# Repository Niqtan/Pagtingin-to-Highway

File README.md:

# Pagtingin (Obstacle Detecting Glasses) 2.0

## Project Aims

The Pagtingin obstacle detecting glasses aims to help visually impaired people to easily detect obstacles in front of them through innovative glasses. While traditional walking sticks indeed help in detecting obstacles on the ground, they often fail to identify objects at chest or head level, such as low-hanging branches, open cabinets, or protruding signs. 

Hence, Pagtingin aims to aid this limitation and ensure a safe journey of navigation. Whether indoors or outdoors, the device will be able to identify potential hazards through a Time-of-Flight sensor and send real-time audio feedback, which helps users to be much more confident and safe in the user's day-to-day lives.

Pagtingin 2.0 uses a modular approach instead of a tightly coupled design, making the system easier to iterate on and refine over time. Some design changes and iterations also have been made.

## Zine
[Click here for beautiful zine page](PAGTINGIN_2.0.pdf)

## Prototype Concept

## PCB 

### Main Module

Image 1. Main PCB Module Front View

Image 2. Main PCB Module Backk View

### Audio Module

Image 3. Audio PCB Module Front View

Image 4. Audio PCB Module Back View

### Sensor Module

Image 5. Sensor PCB Module Front View

Image 6. Sensor PCB Module Back View

## CAD

### Glasses Frame (with new hinges)

Image 7. Glasses Frame Front View

Image 8. Glasses Side View

Image 9. Glasses Frame Back View

### Temples

Image 10. Glasses Rail Side View

Image 11. Glasses Temple Top View

### Module Pod

## 3D Printing
In terms of 3D printing, it might be better to print this in resin since the glasses frame will require precise dimensions. You may be able to print this in FDM, but it is recommended for the parameters to be as precise as possible.

## Making your own glasses!

Phase 1: Ordering the PCB 

For ordering this PCB, I would recommend using JLCPCB as the manufacturer. Use the PCBA assembly option and go through the interface!

Here are some parameters you should know:

Thickness: 0.8 mm or 1.0 mm
Surface finish: HASL (with lead) or ENIG
Copper weight 1 oz

Phase 2: 3D Printing 

Use your favorite slicer and 3D print it up! 

Material for the temples: PETG / PLA
Material for frame: Resin

Once you 3D  print it, you can start assembling it like normal glasses!

Phase 3: Firmware

Flash the firmware with the test code provided.

## BOM

### Main Module
[MainModule.csv](BOM.csv)

### Sensor Module
[SensorModule.csv](BOM3.csv)

### Audio Module
[AudioModule.csv](BOM2.csv)

## Firmware
Still in progress. You may see previous prototypes in the folder for previous version's firmware. But for the firmware, I am planning to use the ESP-IDF in programming it. I chose the ESP-IDF because it allows full control over the ESP32-PICO-D4's peripherals and such. (also because I wanna challenge myself)

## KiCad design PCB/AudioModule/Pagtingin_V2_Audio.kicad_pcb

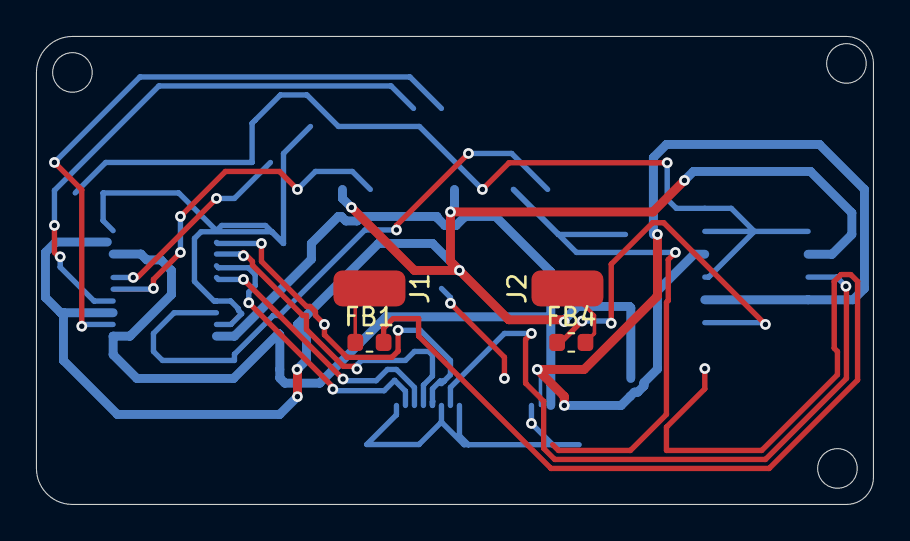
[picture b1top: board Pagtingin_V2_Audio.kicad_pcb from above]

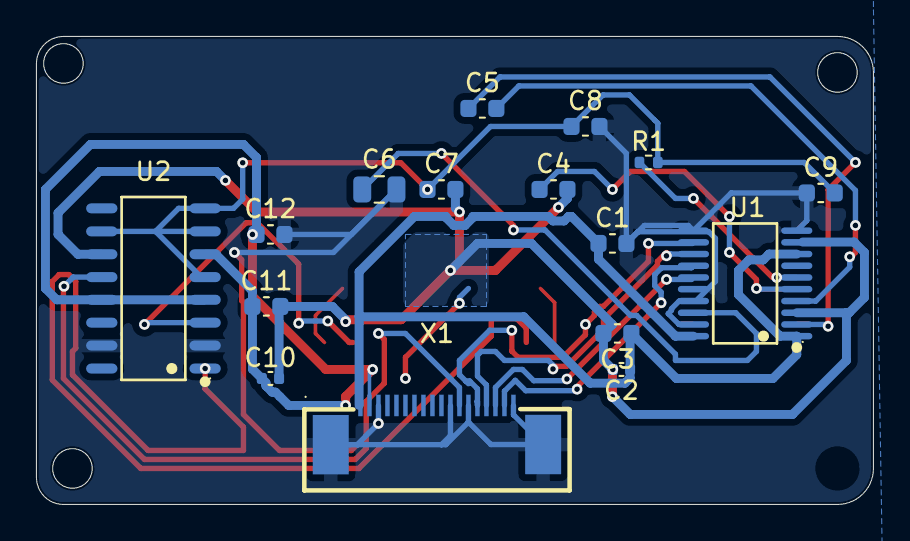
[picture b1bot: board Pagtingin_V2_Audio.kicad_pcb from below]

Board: 2 copper layers, 46.5 x 26.0 mm, 20 parts (16 on the bottom side), 19 nets.

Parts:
C1, C3, C5, C7, C8, C9, C11, C12: 1µ; C_0603_1608Metric
C2, C10: 0.1µ; C_0402_1005Metric
C4: 2.2µ; C_0603_1608Metric
C6: 10µ; C_0805_2012Metric
FB1, FB4: MAF1608FAD151CT000; L_0603_1608Metric
J1, J2: Conn_01x01_Pin; SolderWirePad_1x01_SMD_2x4mm
R1: 1k; R_0402_1005Metric
U1: PCM5102; TSSOP-20_L6.5-W4.4-P0.65-LS6.4-BL
U2: PAM8403DR; SOP-16_L10.0-W3.9-P1.27-LS6.0-BL
X1: AFC07-S18FCA-00; FPC-SMD_AFC07-S18FCA-00

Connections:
+3.3V: C1.1, C2.1, C3.1, U1.1 (CPVDD), U1.8 (AVDD), U1.20 (DVDD), X1.1
+5V: C10.1, C11.1, C12.1, U2.4 (PVDD@1), U2.6 (VDD), U2.13 (PVDD@2), X1.2
/AUDIO_OUT_L: C7.1, C8.1, C9.2, R1.2, U2.5 (MUTE), U2.7 (INL), U2.8 (VREF), U2.10 (INR)
/IO23 (MCU): U2.12 (SHND), X1.12
/IO26 (MCU): U1.12 (SCK), X1.14
/IO27 (MCU): U1.13 (BCK), X1.15
/IO32 (MCU): U1.15 (LRCK), X1.16
/IO33 (MCU): U1.14 (DIN), X1.17
AGround: C2.2, C3.2, C4.2, C7.2, C10.2, C11.2, U1.3 (CPGND), U1.9 (AGND), U2.11 (GND)
GND: C1.2, C6.2, C8.2, C9.1, C12.2, U1.10 (DEMP), U1.11 (FLT), U1.16 (FMT), U1.17 (XSMT), U1.19 (DGND), U2.2 (PGND@1), U2.15 (PGND@2), X1.3, X1.11, X1.13, X1.18, X1.19, X1.20
unnamed: FB1.1, J1.1 (Pin_1_1)
unnamed: FB4.2, J2.1 (Pin_1_1)
unnamed: C5.2, U1.4 (CAPM)
unnamed: C5.1, U1.2 (CAPP)
unnamed: C6.1, U1.18 (LDOO)
unnamed: R1.1, U1.6 (OUTL)
unnamed: C4.1, U1.5 (VNEG)
unnamed: FB1.2, U2.1 (+OUT_L)
unnamed: FB4.1, U2.3 (-OUT_L)

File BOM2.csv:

"Reference","Qty","Value","DNP","Exclude from BOM","Exclude from Board","Footprint","Datasheet","LCSC Part","Price","#"
"C1,C3,C5,C7,C8,C9,C11,C12","8","1µ","","","","Capacitor_SMD:C_0603_1608Metric","","","","1"
"C2,C10","2","0.1µ","","","","Capacitor_SMD:C_0402_1005Metric","","","","2"
"C4","1","2.2µ","","","","Capacitor_SMD:C_0603_1608Metric","","","","3"
"C6","1","10µ","","","","Capacitor_SMD:C_0805_2012Metric","","","","4"
"FB1,FB4","2","MAF1608FAD151CT000","","","","Inductor_SMD:L_0603_1608Metric","","","","5"
"J1,J2","2","Conn_01x01_Pin","","","","Connector_Wire:SolderWirePad_1x01_SMD_2x4mm","","","","6"
"R1","1","1k","","","","Resistor_SMD:R_0402_1005Metric","","","","7"
"U1","1","PCM5102","","","","PCM5102PWR:TSSOP-20_L6.5-W4.4-P0.65-LS6.4-BL","http://www.ti.com/lit/ds/symlink/pcm5102.pdf","","","8"
"U2","1","PAM8403DR","","","","PAM8403:SOP-16_L10.0-W3.9-P1.27-LS6.0-BL","","","None","9"
"X1","1","AFC07-S18FCA-00","","","","AFC07-S18FCA-00:FPC-SMD_AFC07-S18FCA-00","https://www.lcsc.com/datasheet/C262564.pdf","C262564","","10"

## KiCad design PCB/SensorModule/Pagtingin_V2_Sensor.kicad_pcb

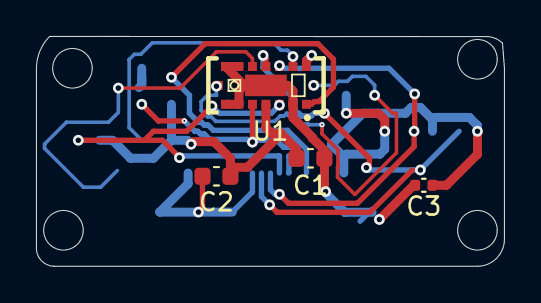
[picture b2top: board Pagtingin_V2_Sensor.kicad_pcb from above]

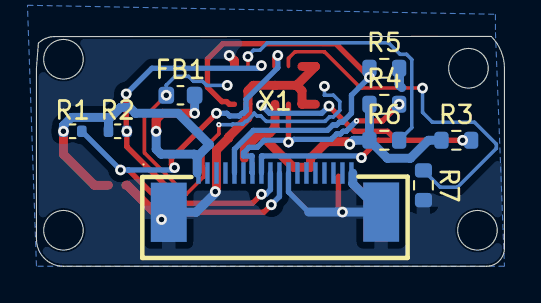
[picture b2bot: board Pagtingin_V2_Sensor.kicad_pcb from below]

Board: 2 copper layers, 26.0 x 12.8 mm, 13 parts (9 on the bottom side), 10 nets.

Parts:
C1, C2: 1µ; C_0603_1608Metric
C3: 0.1µ; C_0402_1005Metric
FB1: MAF1608FAD151CT000; L_0603_1608Metric
R1, R2: 2k2; R_0402_1005Metric
R3, R4, R5, R6: 47k; R_0603_1608Metric
R7: 10k; R_0603_1608Metric
U1: VL53L5CXV0GC_1; LGA-16_L6.4-W3.0_VL53L5CXV0GC-1
X1: AFC07-S18FCA-00; FPC-SMD_AFC07-S18FCA-00

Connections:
+3.3V: C1.1, C2.1, C3.1, FB1.2, R1.1, R2.1, R3.1, R4.1, R6.1, U1.A4 (IOVDD), X1.1
/IO4 (MCU): R5.1, U1.A1 (I2C_RST), X1.5
/IO18 (MCU): R4.2, U1.A5 (LPN), X1.7
/IO19 (MCU): R3.2, U1.A3 (INT), X1.8
/IO21 (MCU): R2.2, U1.C3 (SDA), X1.9
/IO22 (MCU): R1.2, U1.C4 (SCL), X1.10
GND: C1.2, C2.2, C3.2, R5.2, R7.2, U1.A2 (RSVD4), U1.A6 (RSVD1), U1.A7 (RSVD2), U1.B4 (THERMALPAD), U1.C1 (GND), U1.C6 (RSVD3), U1.C7 (GND), X1.3, X1.11, X1.18, X1.19, X1.20
unnamed: FB1.1, U1.B1 (AVDD), U1.B7 (AVDD)
unnamed: R7.1, U1.C5 (RSVD5)
unnamed: R6.2, U1.C2 (RSVD6)

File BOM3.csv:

"Reference","Qty","Value","DNP","Exclude from BOM","Exclude from Board","Footprint","Datasheet","LCSC Part","Price","Availability","#"
"C1,C2","2","1µ","","","","Capacitor_SMD:C_0603_1608Metric","","","","","1"
"C3","1","0.1µ","","","","Capacitor_SMD:C_0402_1005Metric","","","","","2"
"FB1","1","MAF1608FAD151CT000","","","","Inductor_SMD:L_0603_1608Metric","","","","","3"
"R1,R2","2","2k2","","","","Resistor_SMD:R_0402_1005Metric","","","","","4"
"R3,R4,R5,R6","4","47k","","","","Resistor_SMD:R_0603_1608Metric","","","","","5"
"R7","1","10k","","","","Resistor_SMD:R_0603_1608Metric","","","","","6"
"U1","1","VL53L5CXV0GC_1","","","","VL53L5CXV0GC1:LGA-16_L6.4-W3.0_VL53L5CXV0GC-1","","","None","In Stock","7"
"X1","1","AFC07-S18FCA-00","","","","AFC07-S18FCA-00:FPC-SMD_AFC07-S18FCA-00","https://www.lcsc.com/datasheet/C262564.pdf","C262564","","","8"

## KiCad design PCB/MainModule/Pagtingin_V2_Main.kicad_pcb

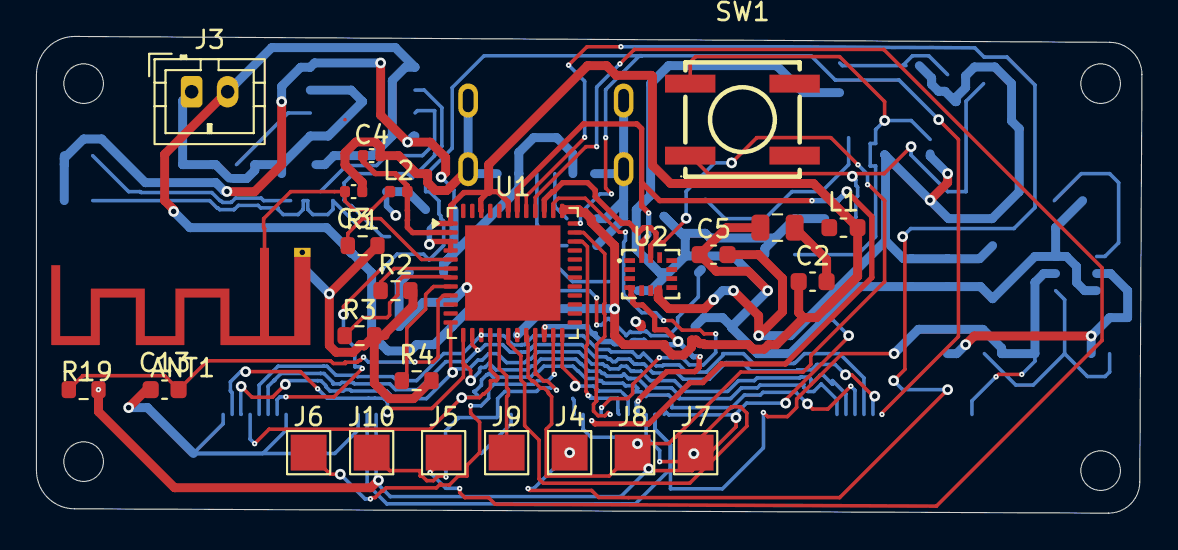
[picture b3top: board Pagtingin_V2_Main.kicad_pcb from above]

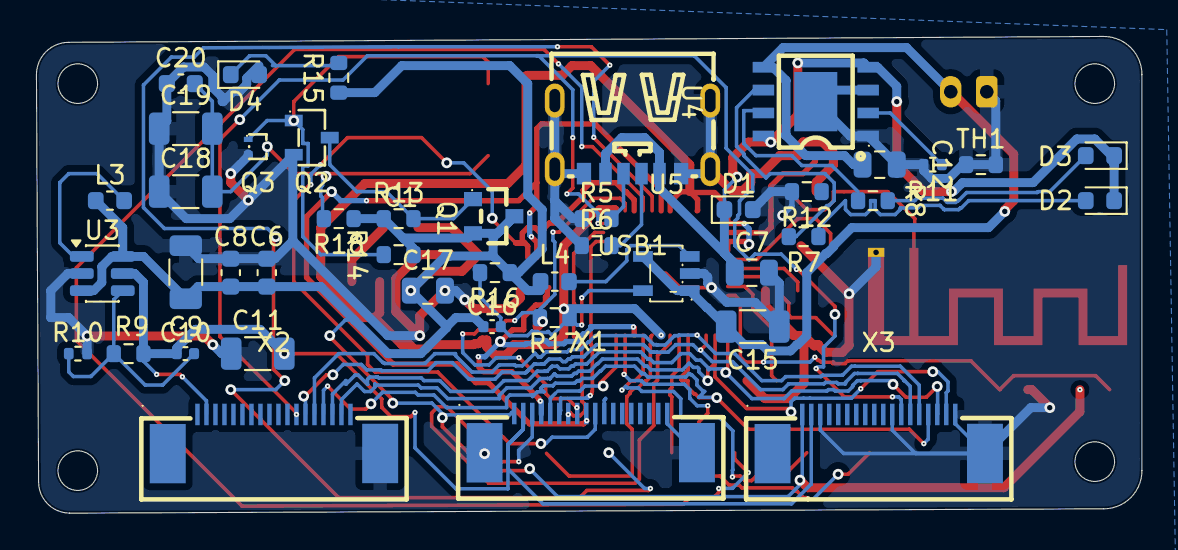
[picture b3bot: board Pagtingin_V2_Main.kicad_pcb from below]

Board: 2 copper layers, 61.4 x 26.5 mm, 69 parts (44 on the bottom side), 49 nets.

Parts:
ANT1: PCB ANTENNA 2.4GHz; Texas_SWRA117D_2.4GHz_Right
C1, C7, C12, C17: 10µ; C_0805_2012Metric
C2, C13: 0.1µ; C_0603_1608Metric
C3: 1.2p; C_0402_1005Metric
C4: 1.5p; C_0402_1005Metric
C5, C6, C8: 1µ; C_0603_1608Metric
C9: 22µ; C_1206_3216Metric
C10: 3.8n; C_0402_1005Metric
C11, C15, C18, C19: 22μ; C_1206_3216Metric
C16: 22p; C_0402_1005Metric
C20: 4.7μ; C_0603_1608Metric
D1: PTVS17VS1UR,115; D_0603_1608Metric
D2, D4: XL-1608PGC-06; LED_0603_1608Metric
D3: XL-1608VRC-06; LED_0603_1608Metric
J3: USE-702528-500PCBJST; JST_PH_B2B-PH-K_1x02_P2.00mm_Vertical
J4, J5, J6, J7, J8, J9, J10: Conn_01x01_Pin; TestPoint_Pad_2.0x2.0mm
L1: 10µ; L_0603_1608Metric
L2: 1.8n; L_0402_1005Metric
L3: 2.5µ; L_0603_1608Metric
L4: 2.2µ; L_0603_1608Metric
Q1: AO3401A; SOT-23_L2.9-W1.3-P1.90-LS2.4-BR
Q2: MMBT2907ALT1G; SOT-23-3_L2.9-W1.3-P1.90-LS2.4-BR
Q3: MMBT2222AM3T5G; SOT-723-3_L1.2-W0.8-P0.80-LS1.2-BR
R1, R2, R3, R4, R12, R19: 10k; R_0603_1608Metric
R5, R6: 56K; R_0603_1608Metric
R7, R8: 1k; R_0603_1608Metric
R9: 47k; R_0603_1608Metric
R10: 4k7; R_0402_1005Metric
R11: 2k; R_0402_1005Metric
R13, R14, R18: 10K; R_0603_1608Metric
R15: 100k; R_0603_1608Metric
R16: 360k; R_0603_1608Metric
R17: 80.6k; R_0603_1608Metric
SW1: KSC441JST2LFS; KEY-SMD_4P-L6.2-W6.2-P4.00-LS6.8
TH1: NCU18XH103F6SRB; R_0603_1608Metric
U1: ESP32-PICO-D4; QFN-48-1EP_7x7mm_P0.5mm_EP5.3x5.3mm
U2: BMI270; LGA-14_L3.0-W2.5-P0.50-BR
U3: TLV61070ADBV; SOT-23-6
U4: TP4056; ESOP-8_L4.9-W3.9-P1.27-LS6.0-BL-EP
U5: RT8059GJ5; SOT-23-5_L3.0-W1.7-P0.95-LS2.8-BR
USB1: TYPE-C 6P; TYPE-C-SMD_TYPE-C-6P_1
X1, X2, X3: AFC07-S18FCA-00; FPC-SMD_AFC07-S18FCA-00

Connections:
+3.3V: C1.1, C5.1, C6.1, C8.1, C9.1, C16.1, C17.1, L1.1, L3.1, L4.2, Q1.2 (S), Q1.3 (D), R13.1, R14.1, R15.1, R16.1, R18.1, R19.1, U2.5 (VDDIO), U2.8 (VDD), U2.12 (CSB), U3.3 (EN), U3.6 (V_{IN}), X1.1, X2.1, X3.1
+3.7V: C12.1, C15.2, J3.2, U4.5 (BAT), U5.1 (EN), U5.4 (VIN)
/+3V3_RF: C2.1, L1.2, U1.1 (VDDA), U1.3 (VDDA3P3), U1.4 (VDDA3P3), U1.19 (VDD3P3_RTC), U1.37 (VDD3P3_CPU), U1.43 (VDDA), U1.46 (VDDA)
/IMU/IO2 (MCU): U1.22 (IO2), U2.4 (INT1), X1.4
/IMU/IO21 (MCU): U1.42 (IO21), U2.14 (SDX), X1.9
/IMU/IO22 (MCU): U1.39 (IO22), U2.13 (SCX), X1.10
/Power System/+5V: C10.1, C11.2, R9.1, U3.5 (V_{OUT}), X1.2, X2.2, X3.2
/Power System/VBUS: C7.1, D1.1 (K), D2.1 (K), D3.1 (K), R12.1, U4.4 (VCC), U4.8 (CE), USB1.A9 (VBUS), USB1.B9 (VBUS)
/Programmer/LNA_IN (MCU): C4.1, L2.2, U1.2 (LNA_IN)
AGround: C1.2, C2.2
GND: ANT1.2, C3.2, C4.2, C5.2, C6.2, C7.2, C8.2, C9.2, C11.1, C12.2, C13.2, C15.1, C17.2, C18.1, C19.1, C20.1, D1.2 (A), D4.2 (A), J3.1, Q2.2 (E), Q3.2 (E), R1.2, R2.2, R3.2, R4.2, R5.1, R6.1, R10.2, R11.1, R12.2, R17.2, TH1.1, TH1.2, U1.49 (GND), U2.6 (GNDIO), U2.7 (GND), U3.2 (GND), U4.1 (TEMP), U4.3 (GND), U4.9 (EP), U5.2 (GND), USB1.7 (EH), USB1.A12 (GND), USB1.B12 (GND), X1.3, X1.11, X1.18, X1.19, X1.20, X2.3, X2.11, X2.18, X2.19, X3.3, X3.11, X3.18, X3.19
unnamed: ANT1.1, C3.1, L2.1
unnamed: D2.2 (A), R7.1
unnamed: D3.2 (A), R8.1
unnamed: D4.1 (K), R15.2
unnamed: J4.1 (Pin_1_1), U1.41 (U0TXD/IO1)
unnamed: J5.1 (Pin_1_1), U1.40 (U0RXD/IO3)
unnamed: J6.1 (Pin_1_1), U1.23 (IO0)
unnamed: J7.1 (Pin_1_1), U1.18 (IO12)
unnamed: J8.1 (Pin_1_1), U1.20 (IO13)
unnamed: J9.1 (Pin_1_1), U1.17 (IO14)
unnamed: J10.1 (Pin_1_1), U1.21 (IO15)
unnamed: Q1.1 (G), Q2.3 (C), R13.2
unnamed: Q2.1 (B), Q3.1 (B), R14.2, SW1.4
unnamed: C18.2, C19.2, C20.2, Q3.3 (C), R18.2, SW1.1
unnamed: C13.1, R19.2, U1.9 (EN)
unnamed: U1.24 (IO4), X1.5
unnamed: U1.34 (IO5), X1.6
unnamed: U1.35 (IO18), X1.7
unnamed: U1.38 (IO19), X1.8
unnamed: U1.36 (IO23), X2.12, X3.12
unnamed: U1.14 (IO25), X2.13, X3.13
unnamed: U1.15 (IO26), X2.14, X3.14
unnamed: U1.16 (IO27), X2.15, X3.15
unnamed: U1.12 (IO32), X2.16, X3.16
unnamed: U1.13 (IO33), X2.17, X3.17
unnamed: R3.1, U1.7 (SENSOR_CAPN)
unnamed: R2.1, U1.6 (SENSOR_CAPP)
unnamed: R4.1, U1.8 (SENSOR_VN)
unnamed: R1.1, U1.5 (SENSOR_VP)
unnamed: L3.2, U3.1 (SW)
unnamed: C10.2, R9.2, R10.1, U3.4 (V_{FB})
unnamed: R11.2, U4.2 (PROG)
unnamed: R8.2, U4.7 (~CHRG)
unnamed: R7.2, U4.6 (~STDBY)
unnamed: C16.2, R16.2, R17.1, U5.5 (FB)
unnamed: L4.1, U5.3 (LLX)
unnamed: R6.2, USB1.A5 (CC1)
unnamed: R5.2, USB1.B5 (CC2)

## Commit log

2025-06-23 initialize
2025-06-23 test image
2025-06-23 added PCB and CAD
2025-06-23 updated Journal
2025-06-23 Added csv file
2025-06-23 updated BOM
2025-06-24 fixed journal
2025-06-27 Implemented new firmware and updated journal
2025-06-30 updated journal and firmware
2025-07-02 Updated journal, main firmware, and Unit testing firmware
2025-07-02 Done unit testing and merged with main
2025-07-03 updated firmware
2025-07-29 fixed some firmware and new problem
2025-08-14 added files
2025-08-30 final conclusion
2026-05-21 V2: Redefining goals
2026-05-27 Entry 01: Starting with reducing the complexity of the project
2026-05-29 Changing up the structure of Pagtingin
2026-05-30 # Entry 03 - 05-30-26 - More ideas + revising the schematic
2026-06-02 # Entry 04 - 06-02-26 - Implementing the FFC Connectors
2026-06-05 # Entry 05 - 06-05-26 - Implementing the FFC Connectors (fr this time)
2026-06-07 # Entry 05 - 06-06-26 - Connecting the IMU to the MCU
2026-06-10 # Entry 07 - 06-10-26 - Back to revising the power system
2026-06-11 # Entry 08 - 06-11-26 - Revising the power system v2
2026-06-12 # Entry 09 - 06-12-26 - Revising the power system v3
2026-06-16 # Entry 10 - 06-16-26 - Revising the audio schematic
2026-06-19 # Entry 11 - 06-16-26 - Making the PCBs for all the modules
2026-06-20 final prototype
2026-06-20 added BOM
2026-06-20 fixed images and stuff
2026-06-23 added steps to replicate!
